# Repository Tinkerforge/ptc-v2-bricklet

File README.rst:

PTC Bricklet 2.0
================

This repository contains the firmware source code and the hardware design
files. The documentation generator configs can be found at
https://github.com/Tinkerforge/generators

Repository Content
------------------

software/:
 * examples/: Examples for all supported languages
 * build/: Compiled files
 * src/: Source code of firmware
 * Makefile: Makefile to build project

hardware/:
 * Contains KiCad project files and additionally schematics as PDF

datasheets/:
 * Contains datasheets for sensors and complex ICs that are used

Hardware
--------

The hardware is designed with the open source EDA Suite KiCad
(http://www.kicad.org). Before you are able to open the files,
you have to install the Tinkerforge kicad-libraries
(https://github.com/Tinkerforge/kicad-libraries). You can either clone
them directly in hardware/ or clone them in a separate folder and
symlink them into hardware/
(ln -s kicad_path/kicad-libraries project_path/hardware). After that you
can open the .pro file in hardware/ with KiCad and from there view and
modify the schematics and the PCB layout.

Software
--------

If you want to do your own Brick/Bricklet firmware development we highly
recommend that you use our build environment setup script and read the
tutorial (https://www.tinkerforge.com/en/doc/Tutorials/Tutorial_Build_Environment/Tutorial.html).

To compile the C code we recommend you to install the newest GNU Arm Embedded
Toolchain (https://launchpad.net/gcc-arm-embedded/+download).
You also need to install bricklib2 (https://github.com/Tinkerforge/bricklib2).

You can either clone it directly in software/src/ or clone it in a
separate folder and symlink it into software/src/
(ln -s bricklib_path/bricklib2 project_path/software/src/). Finally make sure to
have CMake installed (http://www.cmake.org/cmake/resources/software.html).

After that you can build the firmware by invoking make in software/.
The firmware (.zbin) can then be found in software/build/ and uploaded
with brickv (click button "Flashing" on start screen).

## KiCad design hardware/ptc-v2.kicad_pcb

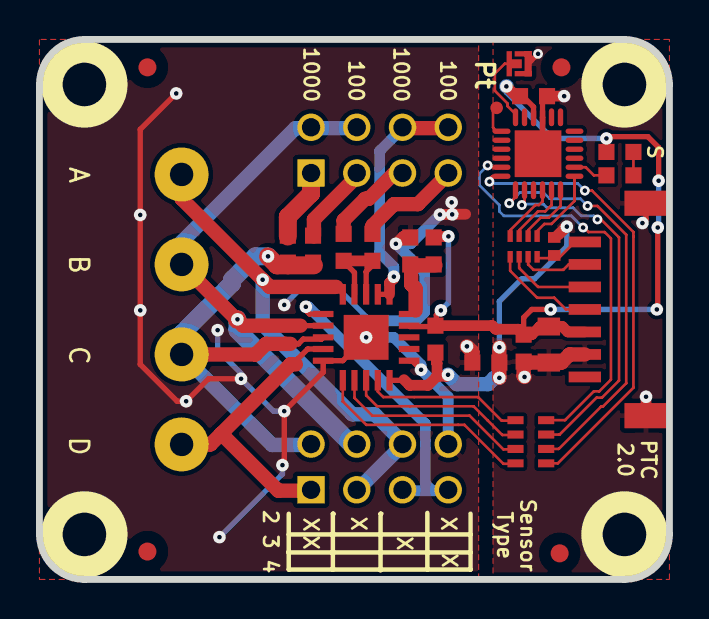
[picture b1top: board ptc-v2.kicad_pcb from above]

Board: 2 copper layers, 35.0 x 30.0 mm, 35 parts (0 on the bottom side), 35 nets.

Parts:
C1: 220pF; C0402F
C2: 10uF; C0805
C3, C4, C5, C6, C8: 100nF; C0603F
C7: 10nF; C0603F
D1: blue; D0603F
FB1, FB2: FB; R0603F
Fiducial_Mark: VAL**; Fiducial_Mark
Fiducial_Mark#2, Fiducial_Mark#3, Fiducial_Mark#4: VAL**; Fiducial_Mark
J1, J2: AKL_5_2
P1: CON-SENSOR; CON-SENSOR2
P2: Debug; DEBUG_PAD
P3: Boot; SolderJumper
P4, P5: CONN_02X04; pin_array_4x2
R1: 1k; R0603F
R2: 390 0.1%; R0603F
R3: 3k9 0.1%; R0603F
RP1: 82; 4X0402
RP2: 100; 0603X4
U1: XMC1100; QFN24-4x4mm-0.5mm
U2: MAX31865; QFN-20-5x5
U3, U4, U5, U6: DRILL; DRILL_NP
VAL: CE_5mm
VAL#2: WEEE_7mm

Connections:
AGND: C6.2, FB1.1, P5.8, U2.10, U2.16, U2.EP
FORCE2: P5.5, P5.7, U2.6
FORCE+: J1.2, P5.3, P5.6, U2.5
FORCE-: J2.1, P5.1, U2.9
GND: C1.2, C2.2, C3.2, C4.2, C5.1, FB1.2, P1.2, P1.EP, P3.1, U1.9, U1.EXP, U2.15
M-CLK: RP2.6, U1.19
M-CS: RP2.7, U1.20
M-MISO: RP2.8, U1.17
M-MOSI: RP2.5, U1.18
unnamed: C1.1, P1.7, RP1.4
unnamed: C6.1, FB2.2, U2.20
unnamed: C7.2, P4.3
unnamed: C8.2, P4.1
unnamed: D1.2, R1.2
unnamed: P1.4, RP1.1
unnamed: P1.5, RP1.2
unnamed: P1.6, RP1.3
unnamed: P2.1, U1.13
unnamed: P3.2, U1.12
unnamed: P4.5, R3.1
unnamed: P4.6, P4.8, U2.1, U2.2
unnamed: P4.7, R2.1
unnamed: R1.1, U1.2
unnamed: R2.2, R3.2, U2.3, U2.4
unnamed: RP2.1, U2.14
unnamed: RP2.2, U2.13
unnamed: RP2.3, U2.12
unnamed: RP2.4, U2.11
RTDIN+: J1.1, P4.2, P4.4, P5.4, U2.7
RTDIN-: C7.1, C8.1, J2.2, P5.2, U2.8
S-CLK: RP1.7, U1.23
S-CS: RP1.8, U1.22
S-MISO: RP1.5, U1.1
S-MOSI: RP1.6, U1.24
VCC: C2.1, C3.1, C4.1, C5.2, D1.1, FB2.1, P1.3, U1.10, U2.19

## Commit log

2018-01-12 add readme
2018-01-15 new prototype hardware added
2018-01-15 fix ground plane
2018-01-15 change default via size
2018-02-08 Add PTC 2.0 software
2018-02-08 Add proper default values for wire mode and filter configuration
2018-02-08 Add API parameter checks
2018-02-20 Cleanup KiCad libraries config
    Ensure LibDir=kicad-libraries and LibName1=tinkerforge.
    Remove special library.
2018-03-05 Remove unused flash-size define
2018-03-15 fix description text
2018-03-27 specify processor
2018-04-12 Add build environment hint to readme
2018-04-12 Add missing colon
2018-04-12 remove note:: for better readability on github
2018-04-12 them -> it
2018-04-16 Add 3d model (*.FCStd & *.step)
2018-04-18 Add sensor connected callback
2018-05-04 Rename files
2018-05-04 Add schematic PDF
2018-06-05 Add examples
2018-06-06 Adapt to bricklib2 callback-value changes to fix wrong threshold min/max type
2018-06-07 Turn debug off
2018-06-07 Update changelog for initial release
2018-06-18 Change capacitor footprint(s) to C0402F
2018-06-19 fix netlist
2018-06-28 Fix readme
2018-07-11 Add Makefile with docker support
2018-07-11 Update directory structure and build instructions
2018-07-11 Remove obsolete generate_makefile scripts
2018-10-04 Increase version for new release (changes in bricklib2)
2018-10-04 Add rev to changelog
2018-10-23 fix resitor footprints, drc
2018-11-06 Add rust examples
2018-11-07 rust: Accept host names for ip connection, fix naming inconsistencies
2018-11-07 rust: Rename callback receivers.
2018-12-14 Add go examples.
2018-12-14 go: Fix printf parameters.
2018-12-18 go: Change import path.
2018-12-18 go: Change import path again.
2018-12-20 rust: Reformat examples.
2019-01-24 mqtt: Add examples.
2019-01-24 mqtt: Fix example header.
2019-01-24 mqtt: Remove executable bit in example permissions.
2019-01-24 go: Minor example fixes.
2019-01-24 mqtt: Minor example fixes.
2019-03-28 mqtt: Fix whitespace.
2019-08-22 c: Adapt to bindings changes
2020-01-13 examples: Use python3 input instead of python2 raw_input.
2020-01-13 examples: mqtt: Remove trailing whitespace.
2020-05-05 fix schematic
2020-08-19 Add uc examples.
2020-08-25 uc: Fix whitespace
2020-08-27 uc: Fix warnings.
2020-09-02 uc: Add example driver note.
2020-10-16 uc: Fix divisor type.
2021-09-20 Fix bug in sensor connected callback delivery logic
    and add 500ms debounce to connected value
2021-09-20 Add rev for v2.0.3
2021-10-25 Update KiCad link
    https://www.kicad.org/blog/2021/10/Avoid-links-to-former-kicad-domain/
2022-04-19 examples: uc: Rename TF_HalContext to TF_HAL.
2022-04-20 Improve MAX31865/SPI error handling
2022-04-20 Add ref for 2.0.4
2022-04-27 uc: Adapt to bindings changes
2022-07-06 Add license files.
2025-01-09 Fix integer overflow in moving average at temperatures above 325°C
2025-01-09 Add ref for 2.0.5

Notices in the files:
hardware/ptc-v2.kicad_pcb:
Licensed under CERN OHL v.1.1
Copyright (©) 2013, B.Nordmeyer
Copyright Tinkerforge GmbH 2013.
This documentation describes Open Hardware and is licensed under the
CERN OHL v. 1.1.
